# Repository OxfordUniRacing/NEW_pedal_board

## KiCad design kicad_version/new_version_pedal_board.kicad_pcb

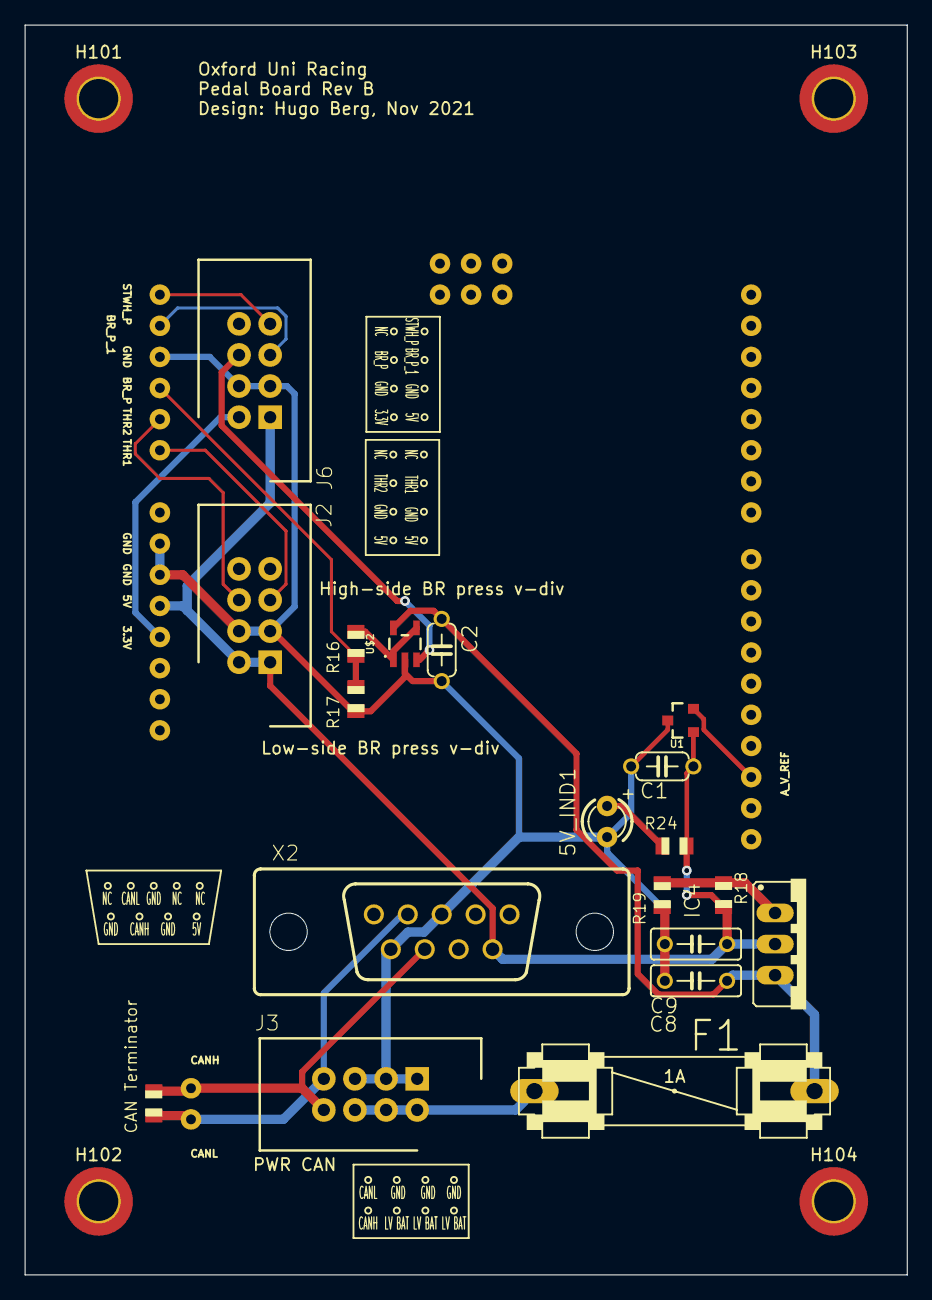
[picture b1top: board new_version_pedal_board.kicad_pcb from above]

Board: 2 copper layers, 72.0 x 102.0 mm, 24 parts (1 on the bottom side), 17 nets.

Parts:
5V_IND1: LED3MM
C1: 0.47uF; C050-024X044
C2: 0.1uF; C050-024X044
C8: 0.1uF; C050-025X075
C9: 1uF; C050-025X075
CAN Terminator: 120; R0805
F1: 1A; FUSE
H101, H102, H103, H104: MountingHole_Pad; MountingHole_3.2mm_M3_DIN965_Pad_TopBottom
IC4: LM317TS; 317TS
J2: THR_1_2; HDRV8W64P254_2X4_1778X895X915P
J3: PWR_CAN; HDRV8W64P254_2X4_1778X895X915P
J6: BR_POS_PRESS_STWH; HDRV8W64P254_2X4_1778X895X915P
R16, R18: 240; R0805
R17: 1K; R0805
R19: 723; R0805
R24: 1.8K; R0805
U1: REF3040AIDBZT; SOT23-3
U$1: SAMC21-XPLAINED-PRO_NO_EXT1&2&3
U$2: TLV170IDBVR; SOT23-5
X2: D-SUB9-H2M09ST; H2M09ST

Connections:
3.3V: J6.2, U$1.J802-3
5V: C1.1, C9.1, IC4.2, J2.1, J2.2, J6.1, R18.2, R24.2, U1.1, U$1.J802-4, X2.9
12V: C2.1, C8.1, F1.2, IC4.3, U$2.5
/INPUTS/12V_BATTERY: F1.1, J3.2, J3.4, J3.6
BR_POSS_1: J6.5, U$1.J803-4
BR_PRESS: R16.1, R17.2, U$1.J803-2
CANH: CAN Terminator.2, J3.8, U$1.CAN-0, X2.7
CANL: CAN Terminator.1, J3.7, U$1.CAN-1, X2.2
GND: 5V_IND1.K, C1.2, C2.2, C8.2, C9.2, J2.3, J2.4, J3.1, J3.3, J3.5, J6.3, J6.4, R17.1, R19.1, U1.3, U$1.J802-5, U$1.J802-6, U$1.J803-3, U$2.2, X2.3, X2.6
unnamed: 5V_IND1.A, R24.1
unnamed: IC4.1, R18.1, R19.2
unnamed: J6.6, U$2.3
unnamed: R16.2, U$2.1, U$2.4
unnamed: U1.2, U$1.J801-7
ST_WH_POSS: J6.7, U$1.J803-5
THR1: J2.5, U$1.J803-0
THR2: J2.6, U$1.J803-1

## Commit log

2022-10-05 PLEASE JUST DOWNLOAD THIS I HATE GIT HUB
